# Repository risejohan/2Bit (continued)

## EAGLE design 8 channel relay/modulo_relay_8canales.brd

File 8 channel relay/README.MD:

# 8 Channel Relay

## Start 🚀

_Be able to use the designs of the common modules to have available and apply to electronic designs._

### Pre requirements 📋

_Relay board is one kind of very popular switch module. You can use it control any devices on or off. This is a DC5V controlled 8 channel relay module. It's high level trigger. Trigger current need not less than 5mA, It can be used in many industry system that using DC5V power supply._

### Conditions and Characteristic🔩
 8-Channel Relay interface board,
 Each one needs 15-20mA Driver Current
 Equiped with high-current relay : DC30V 10A AC250V 10A

It has a DC-DC Step Down LM2596 regulator which is a monolithic integrated circuit suitable for easy and convenient design of a buck type switching source. It is capable of conducting a current of up to 3A. It handles a load with excellent line regulation and low ripple voltage. This device is available with adjustable output voltage

###### Dc-Dc step down
Based on the LM2596 regulator, output between 1.5 and 35Vdc
Input voltage: 4.5-40V
Output voltage: 1.5-35V (Adjustable)
Output current: Maximum 3A
Dimensions: 43 * 20 * 14mm
Switching frequency: 150 KHz

###### Darlingtong
The ULN2803A device is a 50 V, 500 mA Darlington
transistor array. The device consists of eight NPN
Darlington pairs that feature high-voltage outputs with
common-cathode clamp diodes for switching
inductive loads. The collector-current rating of each
Darlington pair is 500 mA. The Darlington pairs may
be connected in parallel for higher current capability

#### Links

- [Lm2596](https://www.ti.com/lit/ds/symlink/lm2596.pdf?ts=1638989805405&ref_url=https%253A%252F%252Fwww.ti.com%252Fproduct%252FLM2596)

- [Darlington Transistor Array](https://www.ti.com/lit/ds/symlink/uln2803a.pdf?ts=1638966404279&ref_url=https%253A%252F%252Fwww.google.com%252F)

- [Relay](https://pdf1.alldatasheet.es/datasheet-pdf/view/1132639/SONGLERELAY/SRD-05VDC-SL-C.html)

- [Photocoupler](https://global.sharp/products/device/lineup/data/pdf/datasheet/PC817XxNSZ1B_e.pdf)

## Built with 🛠️

Development sofware:
[Eagle](https://www.autodesk.com/products/eagle/overview) - Electronic design software

### Components
- LM2596
- ULN2803A
- RELAY
- PHOTOCOUPLER

## Version 📌

For all available versions, look at the [tags in this repository](https://github.com/risejohan/2Bit/tree/main/module%20RTC/ds3231).

## Authors ✒️
* **Johan Riascos** - *Electronic developer* - 
* [Github](https://github.com/risejohan)
* [Instagram Personal](https://instagram.com/johansegura92?utm_medium=copy_link)
* [Instagram 2bit](https://instagram.com/2bit_electronic?utm_medium=copy_link)

You can also look at the list of all the [contributors] (https://github.com/risejohan/2bit/contributors) who have participated in this project.

###  Expressions of gratitude 🎁
---
For the entire community that wishes to add and shows appreciation for sharing knowledge. Welcome to everyone who wishes to contribute in favor of technology.

#### Contributions
If you want to invite us to a coffee ☕ and contribute to continue uploading  content ⬆ . You can do it here 👇🏻
⌨️ con ❤️❤️❤️ [Donation](https://paypal.me/2bitelectronic "Donation") 😊

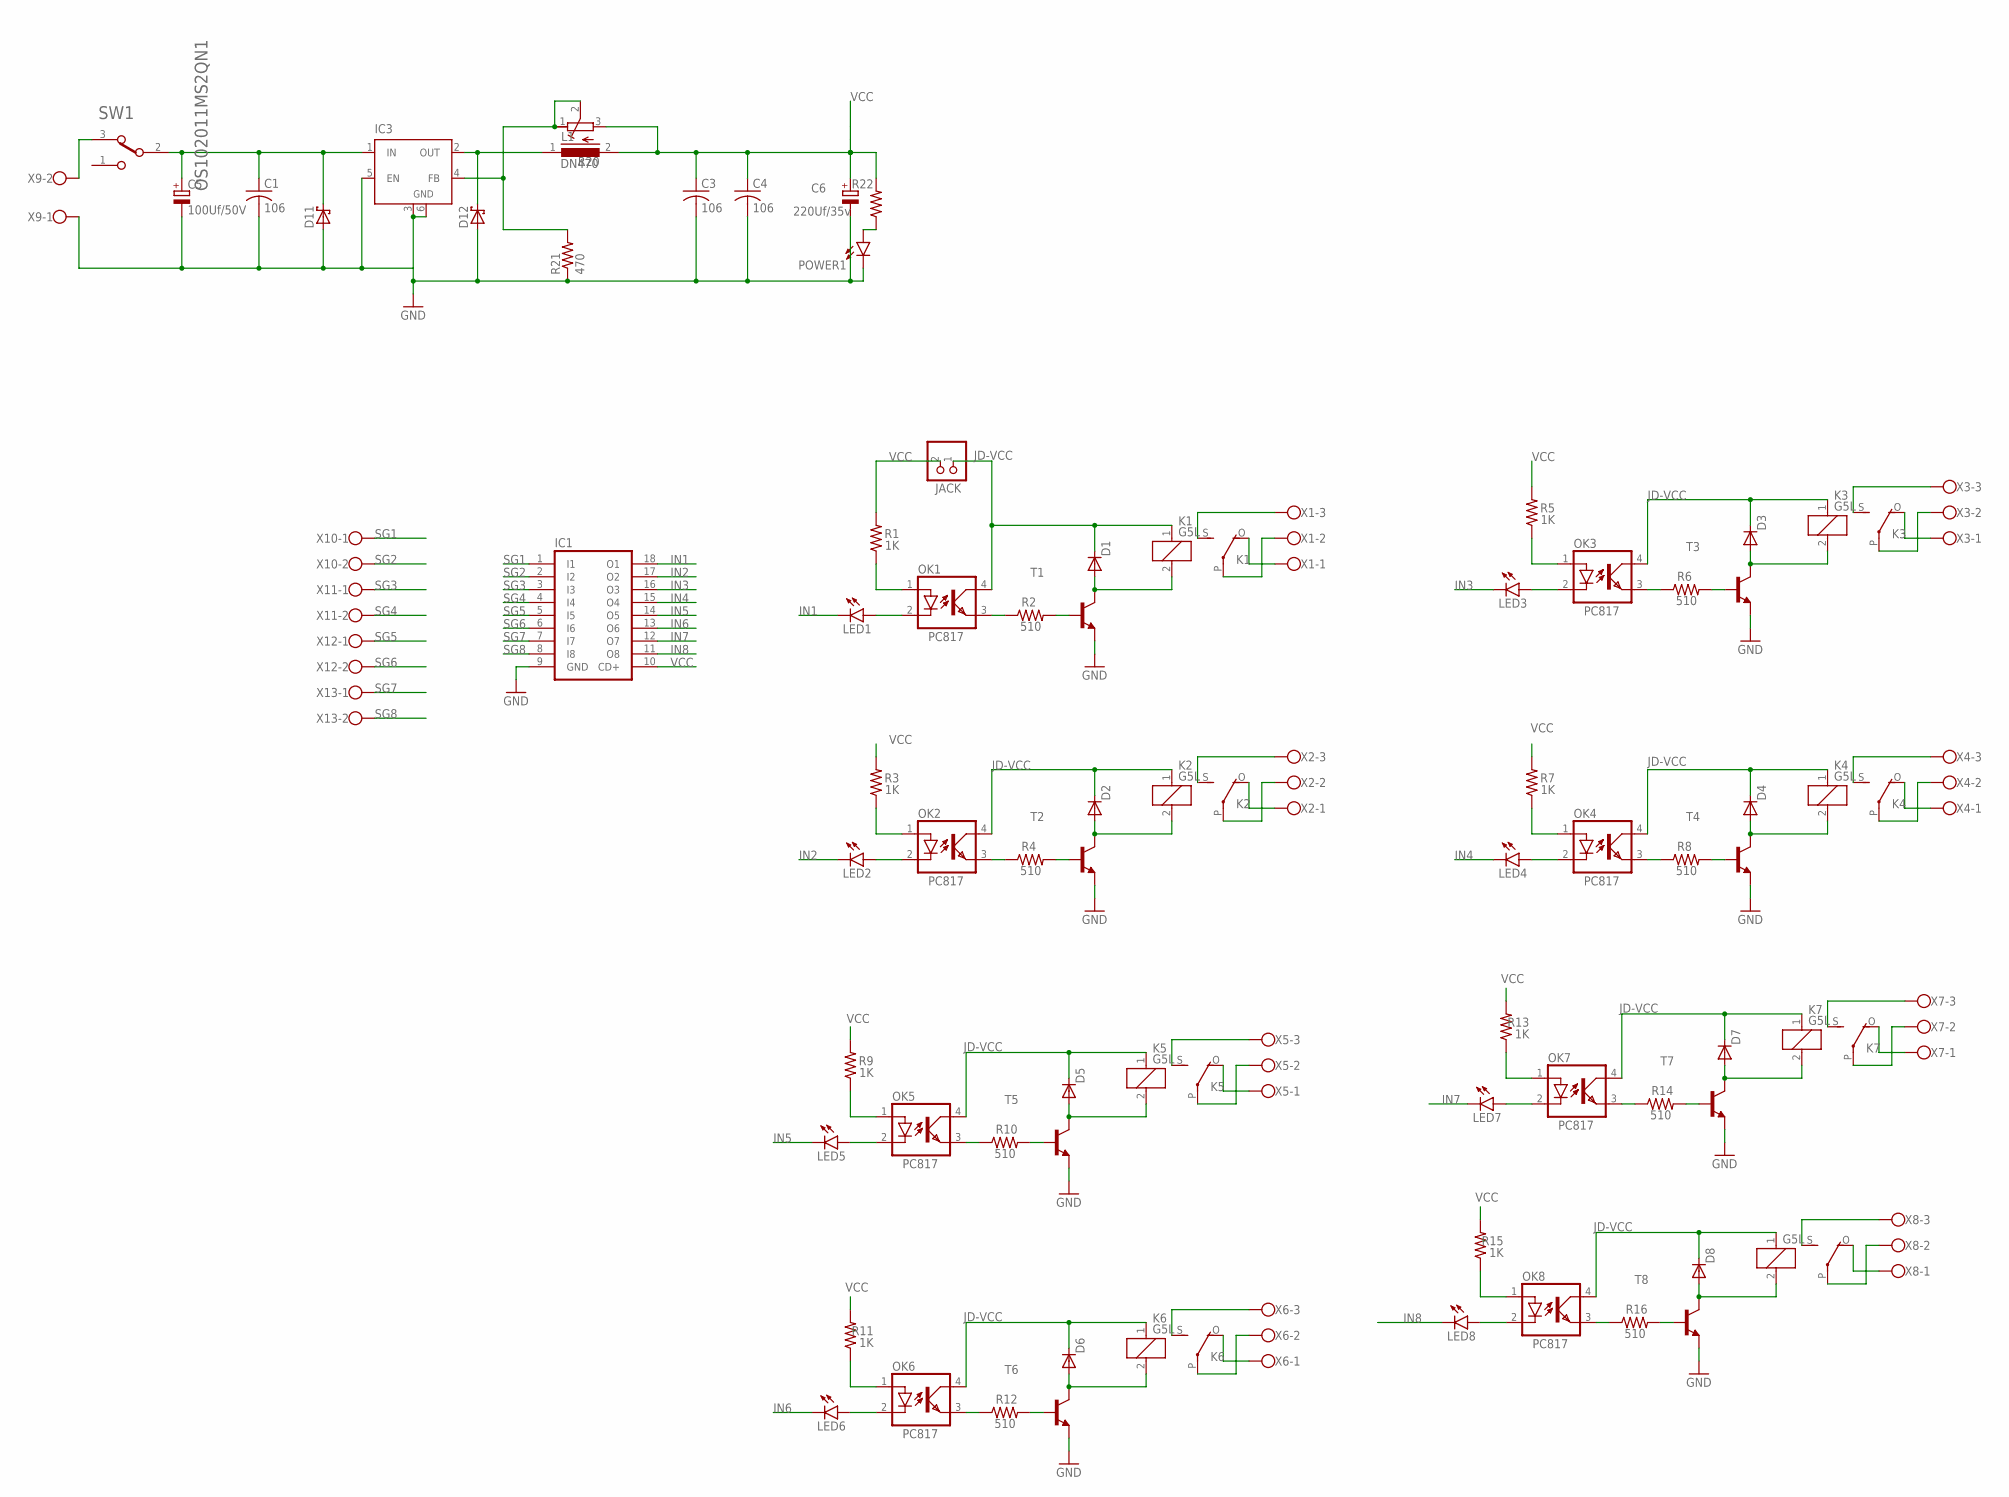
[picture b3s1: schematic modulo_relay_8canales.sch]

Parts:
C1, C3, C4: 106; C0805K
C5: 100Uf/50V; 140CLH-0810
C6: 220Uf/35v; 140CLH-0810
D1, D2, D3, D4, D5, D6, D7, D8: DIODE-DO214AC; DO214AC
D11, D12: SCHOTTKY-DIODE; DIODE_SMB
IC1: ULN2803A; DIL18
IC3: LM2596S; TO263-5
JACK: PINHD-1X2; 1X02
K1, K2, K3, K4, K5, K6, K7, K8: G5L; G5LE
L1: DN470; DR127
LED1, LED2, LED3, LED4, LED5, LED6, LED7, LED8: LEDCHIP-LED0805; CHIP-LED0805
OK1, OK2, OK3, OK4, OK5, OK6, OK7, OK8: PC817; DIL04
POWER1: LEDCHIP-LED0805; CHIP-LED0805
R1, R3, R5, R7, R9, R11, R13, R15: 1K; R0805
R2, R4, R6, R8, R10, R12, R14, R16: 510; R0805
R20: R-TRIMMT93YA; RTRIMT93YA
R21: 470; R0805
R22: 330; R0805
SW1: C&K_COMPONENTS_OS102011MS2QN1C&K_COMPONENTS_OS102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; C&K_COMPONENTS_OS102011MS2QN1_0
T1, T2, T3, T4, T5, T6, T7, T8: MMBT5551LT1-NPN-SOT23-BEC; SOT23-BEC
X1, X2, X3, X4, X5, X6, X7, X8: W237-103
X9, X10, X11, X12, X13: W237-102

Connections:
GND: C1.2, C3.2, C4.2, C5.-, C6.-, D11.A (C), D12.A (C), IC1.9 (GND), IC3.3 (GND), IC3.5 (EN), IC3.6 (GND), POWER1.C, R21.1, T1.E, T2.E, T3.E, T4.E, T5.E, T6.E, T7.E, T8.E, X9.1
IN1: IC1.18 (O1), LED1.C
IN2: IC1.17 (O2), LED2.C
IN3: IC1.16 (O3), LED3.C
IN4: IC1.15 (O4), LED4.C
IN5: IC1.14 (O5), LED5.C
IN6: IC1.13 (O6), LED6.C
IN7: IC1.12 (O7), LED7.C
IN8: IC1.11 (O8), LED8.C
IN9: C1.1, C5.+, D11.C (A), IC3.1 (IN), SW1.2
JD-VCC: D1.C, D2.C, D3.C, D4.C, D5.C, D6.C, D7.C, D8.C, JACK.1, K1.1, K2.1, K3.1, K4.1, K5.1, K6.1, K7.1, K8.1, OK1.4 (COL), OK2.4 (COL), OK3.4 (COL), OK4.4 (COL), OK5.4 (COL), OK6.4 (COL), OK7.4 (COL), OK8.4 (COL)
unnamed: OK1.3 (EMIT), R2.1
unnamed: OK1.1 (A), R1.1
unnamed: LED1.A, OK1.2 (C)
unnamed: OK7.3 (EMIT), R14.1
unnamed: R2.2, T1.B
unnamed: D1.A, K1.2, T1.C
unnamed: K1.S, X1.3
unnamed: K1.P, X1.2
unnamed: K1.O, X1.1
unnamed: OK2.3 (EMIT), R4.1
unnamed: OK2.1 (A), R3.1
unnamed: LED2.A, OK2.2 (C)
unnamed: OK7.1 (A), R13.1
unnamed: R4.2, T2.B
unnamed: D2.A, K2.2, T2.C
unnamed: K2.S, X2.3
unnamed: K2.P, X2.2
unnamed: K2.O, X2.1
unnamed: OK3.3 (EMIT), R6.1
unnamed: OK3.1 (A), R5.1
unnamed: LED3.A, OK3.2 (C)
unnamed: LED7.A, OK7.2 (C)
unnamed: R6.2, T3.B
unnamed: D3.A, K3.2, T3.C
unnamed: K3.S, X3.3
unnamed: K3.P, X3.2
unnamed: K3.O, X3.1
unnamed: OK4.3 (EMIT), R8.1
unnamed: OK4.1 (A), R7.1
unnamed: LED4.A, OK4.2 (C)
unnamed: R14.2, T7.B
unnamed: R8.2, T4.B
unnamed: D4.A, K4.2, T4.C
unnamed: K4.S, X4.3
unnamed: K4.P, X4.2
unnamed: K4.O, X4.1
unnamed: OK5.3 (EMIT), R10.1
unnamed: OK5.1 (A), R9.1
unnamed: LED5.A, OK5.2 (C)
unnamed: D7.A, K7.2, T7.C
unnamed: R10.2, T5.B
unnamed: D5.A, K5.2, T5.C
unnamed: K5.S, X5.3
unnamed: K5.P, X5.2
unnamed: K5.O, X5.1
unnamed: OK6.3 (EMIT), R12.1
unnamed: OK6.1 (A), R11.1
unnamed: LED6.A, OK6.2 (C)
unnamed: K7.S, X7.3
unnamed: R12.2, T6.B
unnamed: D6.A, K6.2, T6.C
unnamed: K6.S, X6.3
unnamed: K6.P, X6.2
unnamed: K6.O, X6.1
unnamed: K7.P, X7.2
unnamed: K7.O, X7.1
unnamed: OK8.3 (EMIT), R16.1
unnamed: OK8.1 (A), R15.1
unnamed: LED8.A, OK8.2 (C)
unnamed: R16.2, T8.B
unnamed: D8.A, K8.2, T8.C
unnamed: K8.S, X8.3
unnamed: K8.P, X8.2
unnamed: K8.O, X8.1
unnamed: SW1.3, X9.2
unnamed: D12.C (A), IC3.2 (OUT), L1.1
unnamed: IC3.4 (FB), R20.1 (E), R20.2 (S), R21.2
unnamed: POWER1.A, R22.1
SG1: IC1.1 (I1), X10.1
SG2: IC1.2 (I2), X10.2
SG3: IC1.3 (I3), X11.1
SG4: IC1.4 (I4), X11.2
SG5: IC1.5 (I5), X12.1
SG6: IC1.6 (I6), X12.2
SG7: IC1.7 (I7), X13.1
SG8: IC1.8 (I8), X13.2
VCC: C3.1, C4.1, C6.+, IC1.10 (CD+), JACK.2, L1.2, R1.2, R3.2, R5.2, R7.2, R9.2, R11.2, R13.2, R15.2, R20.3 (A), R22.2

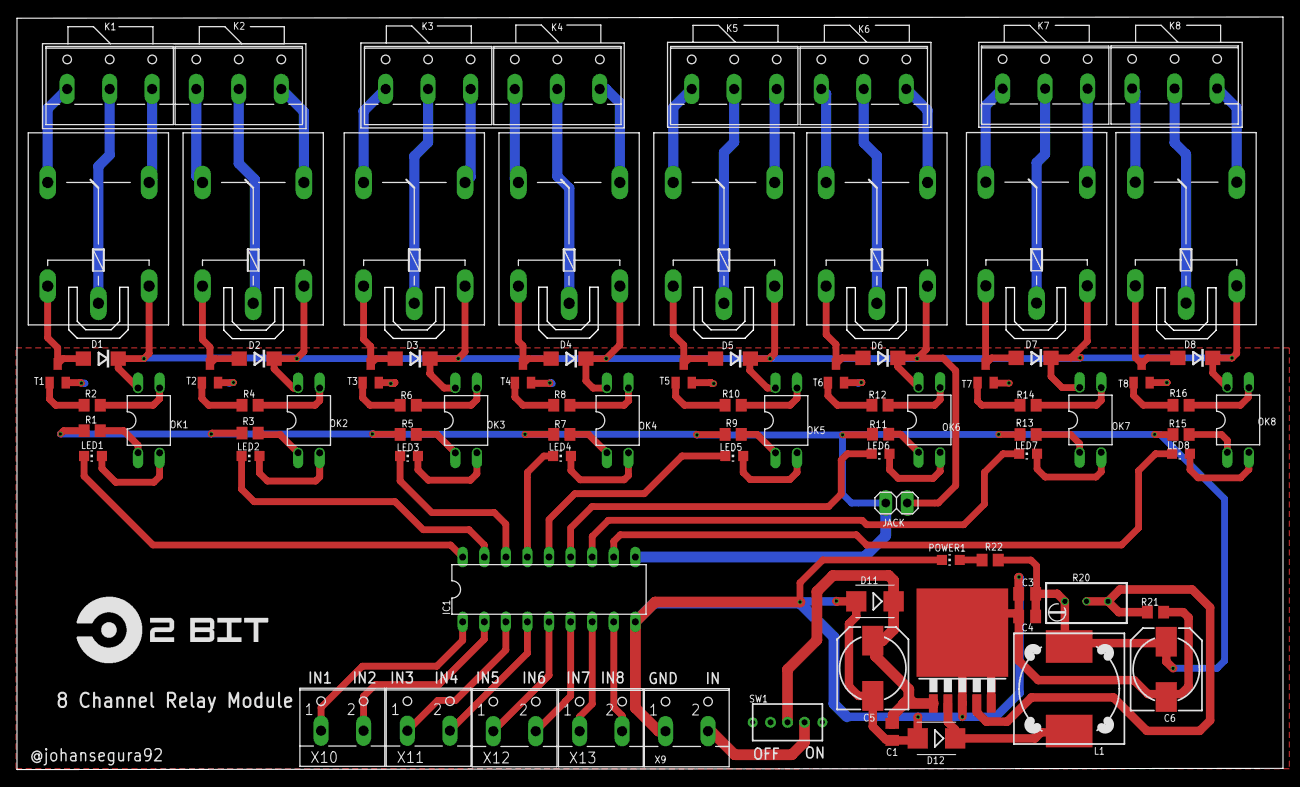
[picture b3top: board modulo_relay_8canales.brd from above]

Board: 2 copper layers, 149.0 x 88.6 mm, 85 parts (0 on the bottom side), 88 nets.

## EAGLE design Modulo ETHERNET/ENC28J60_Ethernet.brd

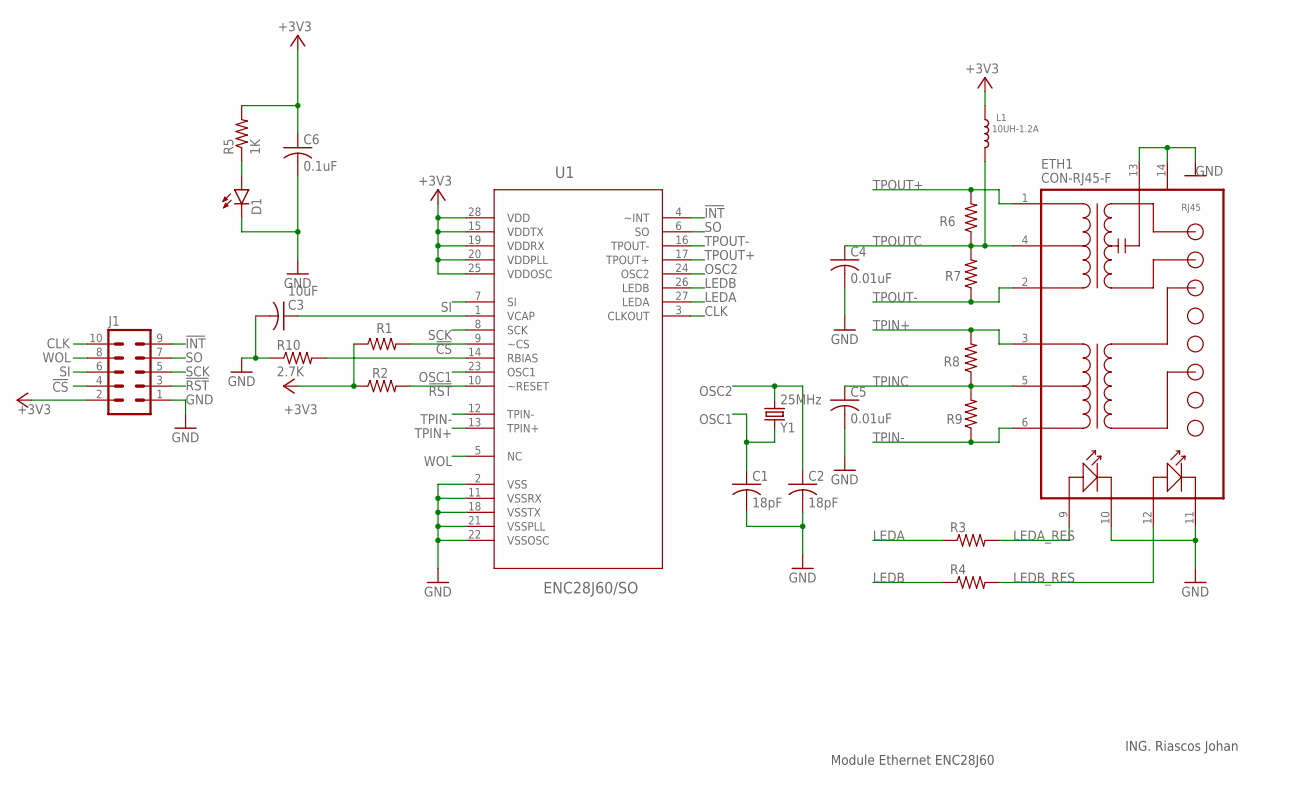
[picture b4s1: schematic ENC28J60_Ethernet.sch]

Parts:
C1, C2: 18pF; C0805
C3: 10uF; C1210
C4, C5: 0.01uF; C0805
C6: 0.1uF; C0805
D1: LEDCHIP-LED0805; CHIP-LED0805
ETH1: CON-RJ45-F; HR911105A
J1: MA05-2
L1: 10UH-1.2A; L0805
R1, R2: R-US_R0805; R0805
R3, R4, R5: 1K; R0805
R6, R7, R8, R9: 50R; R0805
R10: 2.7K; R0805
U1: ENC28J60/SO; SOIC127P1034X264-28N
Y1: 25MHz; HC49/S

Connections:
3.3V: C6.1, J1.2, L1.1, R1.1, R2.1, R5.2, U1.15 (VDDTX), U1.19 (VDDRX), U1.20 (VDDPLL), U1.25 (VDDOSC), U1.28 (VDD)
!CS!: J1.4, R1.2, U1.9 (~CS)
!INT!: J1.9, U1.4 (~INT)
!RST!: J1.3, R2.2, U1.10 (~RESET)
CLK: J1.10, U1.3 (CLKOUT)
GND: C1.2, C2.2, C3.2, C4.2, C5.2, C6.2, D1.C, ETH1.10, ETH1.11, ETH1.13, ETH1.14, J1.1, R10.1, U1.2 (VSS), U1.11 (VSSRX), U1.18 (VSSTX), U1.21 (VSSPLL), U1.22 (VSSOSC)
LEDA: R3.1, U1.27 (LEDA)
LEDA_RES: ETH1.9, R3.2
LEDB: R4.1, U1.26 (LEDB)
LEDB_RES: ETH1.12, R4.2
unnamed: D1.A, R5.1
OSC1: C1.1, U1.23 (OSC1), Y1.1
OSC2: C2.1, U1.24 (OSC2), Y1.2
RBIAS: R10.2, U1.14 (RBIAS)
SCK: J1.5, U1.8 (SCK)
SI: J1.6, U1.7 (SI)
SO: J1.7, U1.6 (SO)
TPIN+: ETH1.3, R8.2, U1.13 (TPIN+)
TPIN-: ETH1.6, R9.1, U1.12 (TPIN-)
TPINC: C5.1, ETH1.5, R8.1, R9.2
TPOUT+: ETH1.1, R6.2, U1.17 (TPOUT+)
TPOUT-: ETH1.2, R7.1, U1.16 (TPOUT-)
TPOUTC: C4.1, ETH1.4, L1.2, R6.1, R7.2
VCAP: C3.1, U1.1 (VCAP)
WOL: J1.8, U1.5 (NC)

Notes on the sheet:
ING. Riascos Johan
Module Ethernet ENC28J60

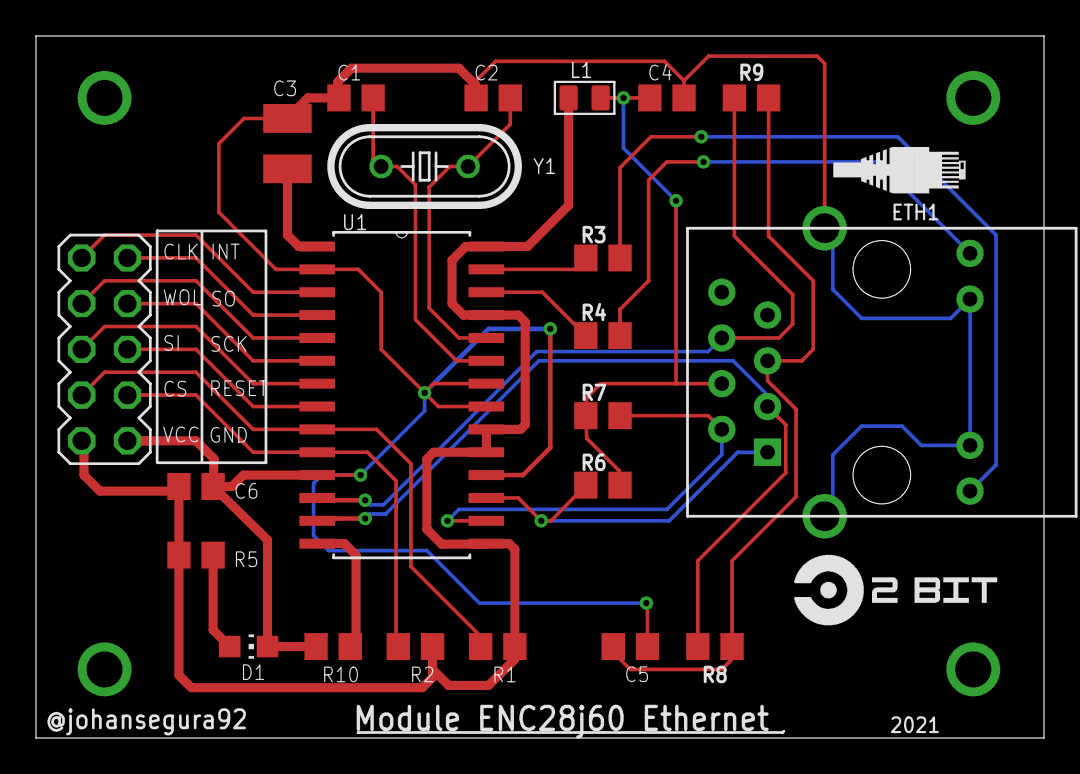
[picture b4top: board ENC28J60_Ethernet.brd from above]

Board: 2 copper layers, 56.0 x 39.0 mm, 22 parts (0 on the bottom side), 25 nets.

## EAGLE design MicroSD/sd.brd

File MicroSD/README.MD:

# SD Module

## Start 🚀

_Be able to use the designs of the common modules to have available and apply to electronic designs._

### Pre requirements 📋

_SD and micro SD cards have become a standard, displacing other data storage media due to their large capacity and small size. For this reason they have been integrated into a large number of devices, currently being frequent components in computers, tablets and smartphones, among others._

_Within the world of Arduino, it is possible to find low cost readers for both SD and micro SD cards. The first to appear were the SD readers and later the micro SD ones. Therefore, in general, the modules with micro SD are more modern models than those of SD_

_In both types of readers, the reading can be done through the SPI bus. Although they may have other interfaces, such as I2C or UART bus, it is usually preferable to use SPI due to its high transfer rate._

### Conditions and Characteristic🔩

##### Connection SPI

4-wire SPI devices have four signals:
- Clock (SPI CLK, SCLK)
- Chip select (CS)
- Master out, slave in (MOSI)
- Master in, slave out (MISO)

###### Data
The SD format includes five versions of cards, available in three sizes. The five families are:

- "Standard Capacity" (SDSC), the original, "standard capacity",
- "High Capacity" (SDHC), "high capacity",
- "Extended Capacity" (SDXC), "extended capacity",
- “Input / Output” (SDIO), «input / output»,
- "Ultra Capacity" (SDUC), "Ultra Capacity"

The three sizes are:

- Original standard SD,
- miniSD,
- micro SD.

Chip Quadruple Bus Buffer Gate With 3-State Outputs, Inputs can be driven from either 3.3-V or 5-V devices. This feature allows the use of this device as a translator in a mixed 3.3-V/5-V system environment.

**Note: The module doesn´t have a 5V or 3.3V regulator, it is necessary to be able to supply it for its correct operation.**

#### Links

- [SN74LVC125A](https://www.ti.com/lit/ds/symlink/sn74lvc125a.pdf?ts=1639008407340&ref_url=https%253A%252F%252Fwww.google.com%252F)

## Built with 🛠️

Development sofware:
[Eagle](https://www.autodesk.com/products/eagle/overview) - Electronic design software

## Version 📌

For all available versions, look at the [tags in this repository](https://github.com/risejohan/2Bit/tree/main/module%20RTC/ds3231).

## Authors ✒️
* **Johan Riascos** - *Electronic developer* - 
* [Github](https://github.com/risejohan)
* [Instagram Personal](https://instagram.com/johansegura92?utm_medium=copy_link)
* [Instagram 2bit](https://instagram.com/2bit_electronic?utm_medium=copy_link)

You can also look at the list of all the [contributors] (https://github.com/risejohan/2bit/contributors) who have participated in this project.

###  Expressions of gratitude 🎁
---
For the entire community that wishes to add and shows appreciation for sharing knowledge. Welcome to everyone who wishes to contribute in favor of technology.

#### Contributions
If you want to invite us to a coffee ☕ and contribute to continue uploading  content ⬆ . You can do it here 👇🏻
⌨️ con ❤️❤️❤️ [Donation](https://paypal.me/2bitelectronic "Donation") 😊

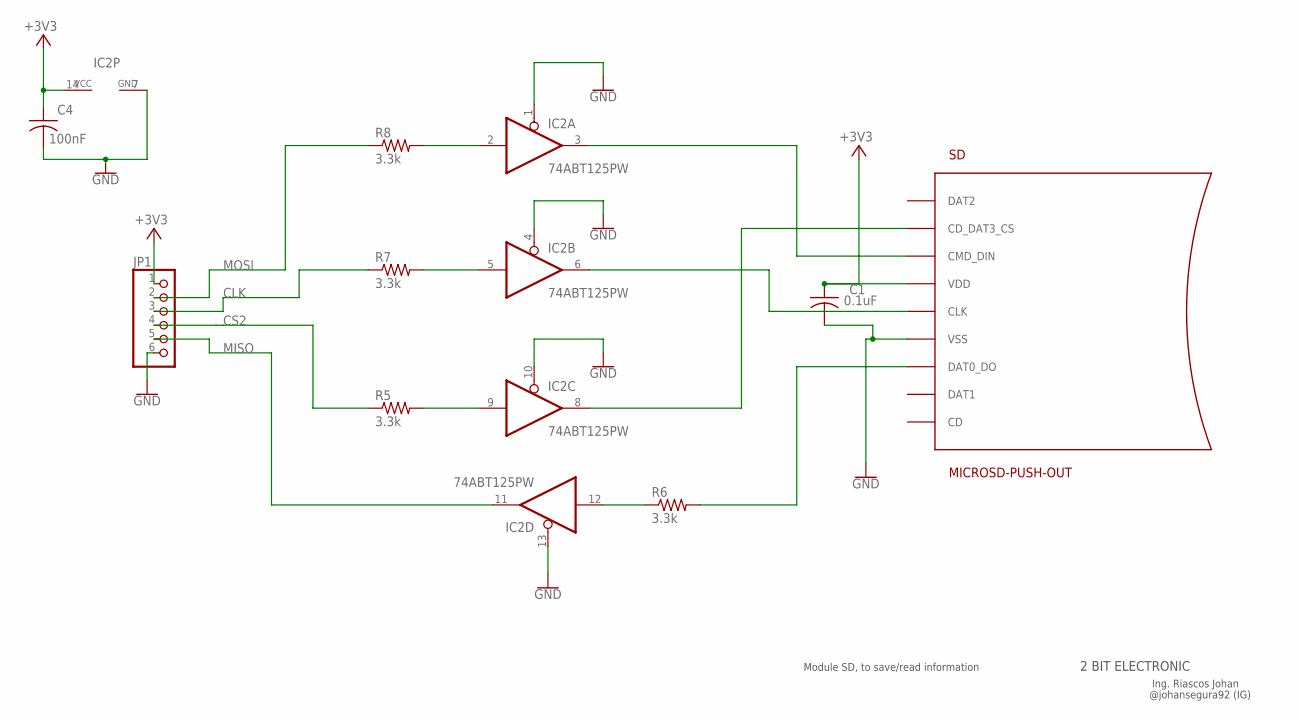
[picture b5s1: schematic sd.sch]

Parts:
C1: 0.1uF; C0603
C4: 100nF; C0603
IC2: 74ABT125PW; TSSOP14
JP1: PINHD-1X6; 1X06
R5, R6, R7, R8: 3.3k; R0603
SD: MICROSD-PUSH-OUT

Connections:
+3V3: C1.1, C4.1, IC2.14 (VCC), JP1.1, SD.4 (VDD)
CLK: JP1.3, R7.1
CS2: JP1.4, R5.1
GND: C1.2, C4.2, IC2.1 (OE), IC2.4 (OE), IC2.7 (GND), IC2.10 (OE), IC2.13 (OE), JP1.6, SD.6 (VSS), SD.G1 (VSS), SD.G2 (VSS), SD.G3 (VSS), SD.G4 (VSS)
MISO: IC2.11 (O), JP1.5
MOSI: JP1.2, R8.1
unnamed: IC2.2 (I), R8.2
unnamed: IC2.5 (I), R7.2
unnamed: IC2.9 (I), R5.2
unnamed: IC2.12 (I), R6.1
unnamed: IC2.8 (O), SD.2 (CD_DAT3_CS)
unnamed: IC2.3 (O), SD.3 (CMD_DIN)
unnamed: IC2.6 (O), SD.5 (CLK)
unnamed: R6.2, SD.7 (DAT0_DO)

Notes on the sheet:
2 BIT ELECTRONIC
@johansegura92 (IG)
Ing. Riascos Johan
Module SD, to save/read information

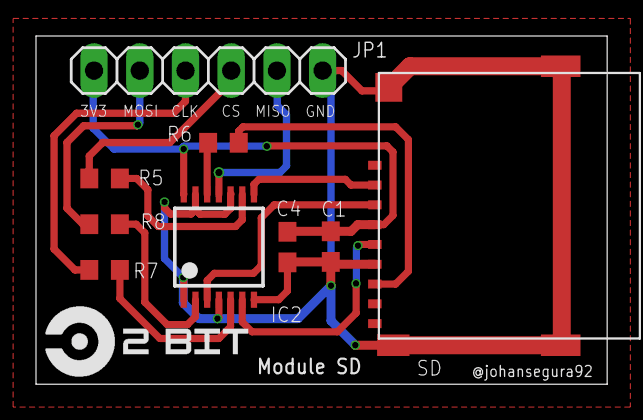
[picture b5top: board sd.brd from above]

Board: 2 copper layers, 31.7 x 19.3 mm, 9 parts (0 on the bottom side), 14 nets.

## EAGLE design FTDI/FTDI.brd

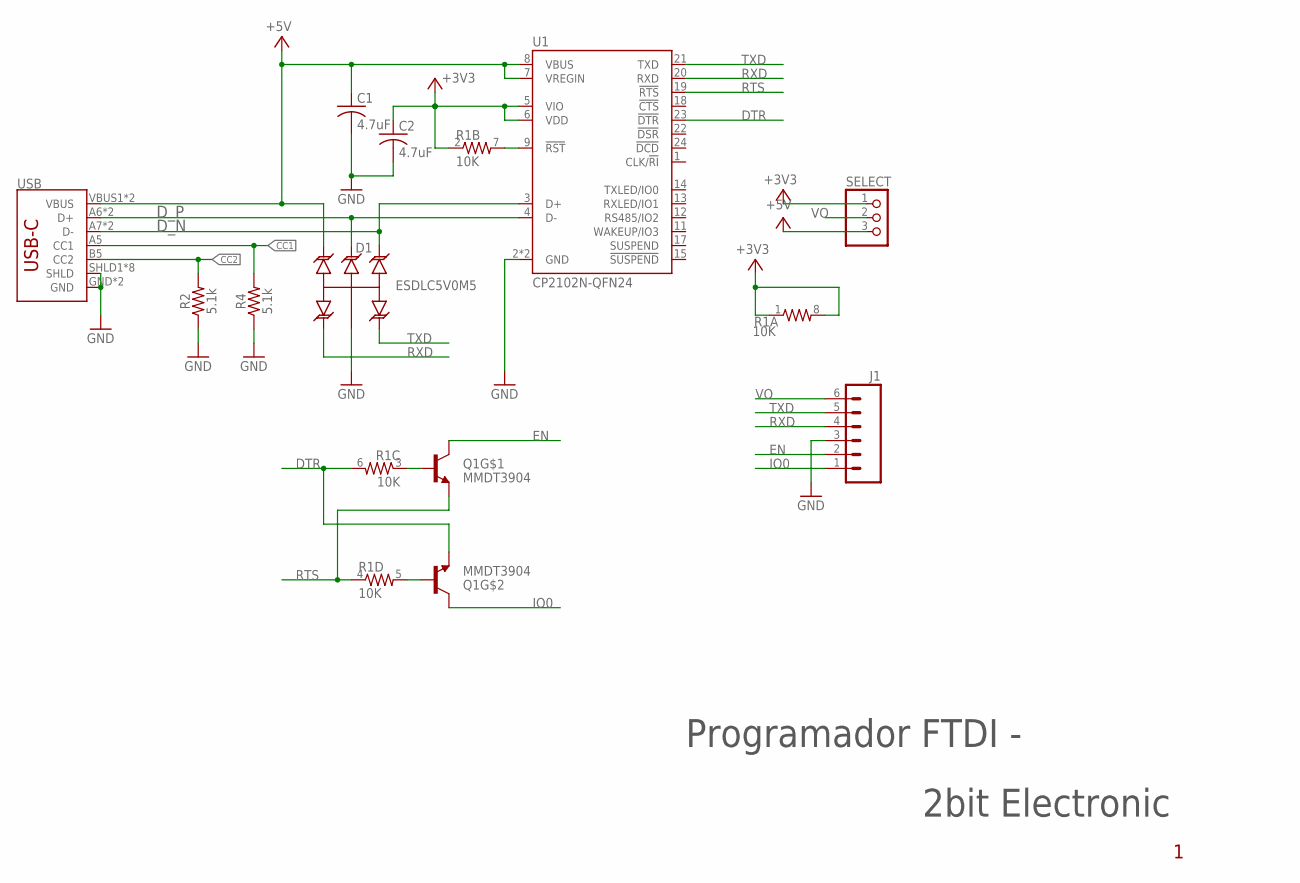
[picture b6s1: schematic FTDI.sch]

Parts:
C1, C2: 4.7uF; C0603K
D1: ESDLC5V0M5; SOT-563
J1: M06SILK_FEMALE_PTH; 1X06
Q1: MMDT3904; SOT363
R1: 10K; 0603-ARV
R2, R4: 5.1k; 0603
SELECT: PINHD-1X3; 1X03
U1: CP2102N-QFN24; QFN24G-0.5-4X4MM
USB: USB_C16PIN; USB-C-16P

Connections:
+3V3: C2.1, R1.1, R1.2 (1), R1.8 (2), SELECT.1, U1.5 (VIO), U1.6 (VDD)
+5V: C1.1, D1.6 (C1), SELECT.3, U1.7 (VREGIN), U1.8 (VBUS), USB.VBUS1 (VBUS), USB.VBUS2 (VBUS)
CC1: R4.2, USB.A5 (CC1)
CC2: R2.2, USB.B5 (CC2)
DTR: Q1.4 (E), R1.6 (2), U1.23 (!DTR)
D_N: D1.4 (C3), U1.3 (D+), USB.A7 (D-), USB.B7 (D-)
D_P: D1.5 (C2), U1.4 (D-), USB.A6 (D+), USB.B6 (D+)
EN: J1.2, Q1.6 (C)
GND: C1.2, C2.2, D1.2 (A), J1.3, R2.1, R4.1, U1.2 (GND), U1.E (GND), USB.GND, USB.GND2 (GND), USB.SHLD1 (SHLD), USB.SHLD2 (SHLD), USB.SHLD3 (SHLD), USB.SHLD4 (SHLD), USB.SHLD5 (SHLD), USB.SHLD6 (SHLD), USB.SHLD7 (SHLD), USB.SHLD8 (SHLD)
IO0: J1.1, Q1.3 (C)
unnamed: R1.7 (2), U1.9 (!RST)
unnamed: Q1.2 (B), R1.3 (1)
unnamed: Q1.5 (B), R1.5 (2)
RTS: Q1.1 (E), R1.4 (1), U1.19 (!RTS)
RXD: D1.1 (C4), J1.4, U1.20 (RXD)
TXD: D1.3 (C5), J1.5, U1.21 (TXD)
VO: J1.6, SELECT.2

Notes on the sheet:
Programador FTDI -
2bit Electronic

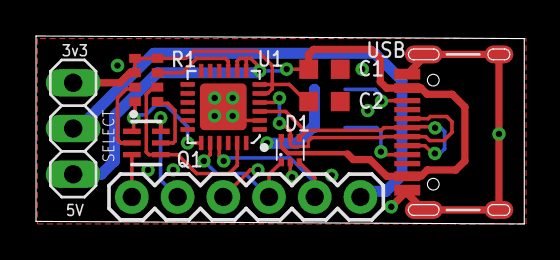
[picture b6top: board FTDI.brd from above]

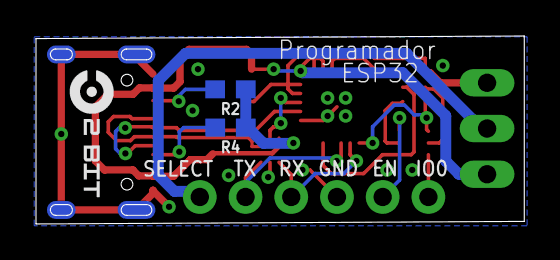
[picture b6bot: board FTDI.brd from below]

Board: 2 copper layers, 27.1 x 10.4 mm, 11 parts (2 on the bottom side), 17 nets.

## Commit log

2021-11-19 Change component
    modification of components, connector type C
2021-11-19 change components
2021-11-19 add select
2021-11-23 Riel din
2021-11-25 Module Sd
    Save/ read Information in Sd Card
2021-11-26 Module Ethernet
    ENC28J60
2021-11-29 channel relay
    Module
2021-12-06 Module lm2596
    DC- DC STEP DOWN
2021-12-07 Module RTC
2021-12-07 Module RTC
    Desing in Kicad
2021-12-07 Create README.MD
    Description Module
2021-12-07 update Readme
    Explain model
2021-12-08 update readme.md
    update readme
2021-12-08 Logo
2021-12-10 Battery charger
    Module Battery charger 18650
2021-12-10 add schematic complete
2021-12-15 Voice Module
    Create Voice Module
2021-12-16 Ruler PCB
2021-12-21 Node LoRa
2021-12-21 add images
2022-01-11 Module Ethernet - modbus
2022-06-18 Simulation Proteus
    Software simulation for watchdog timmer
